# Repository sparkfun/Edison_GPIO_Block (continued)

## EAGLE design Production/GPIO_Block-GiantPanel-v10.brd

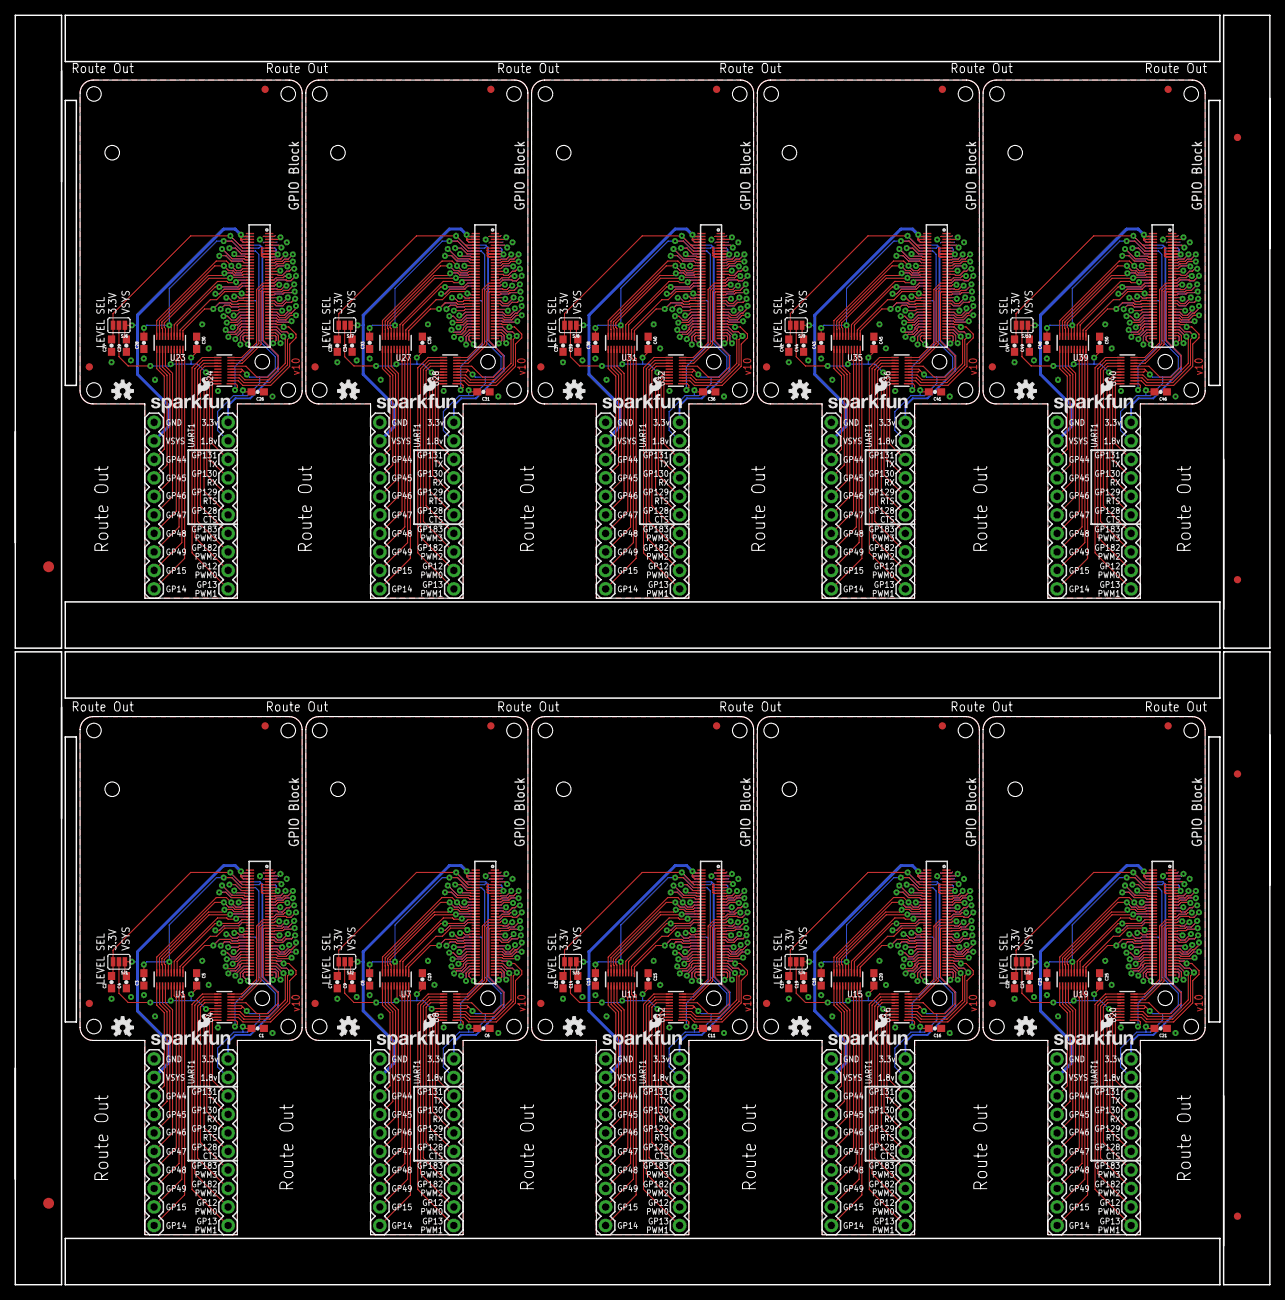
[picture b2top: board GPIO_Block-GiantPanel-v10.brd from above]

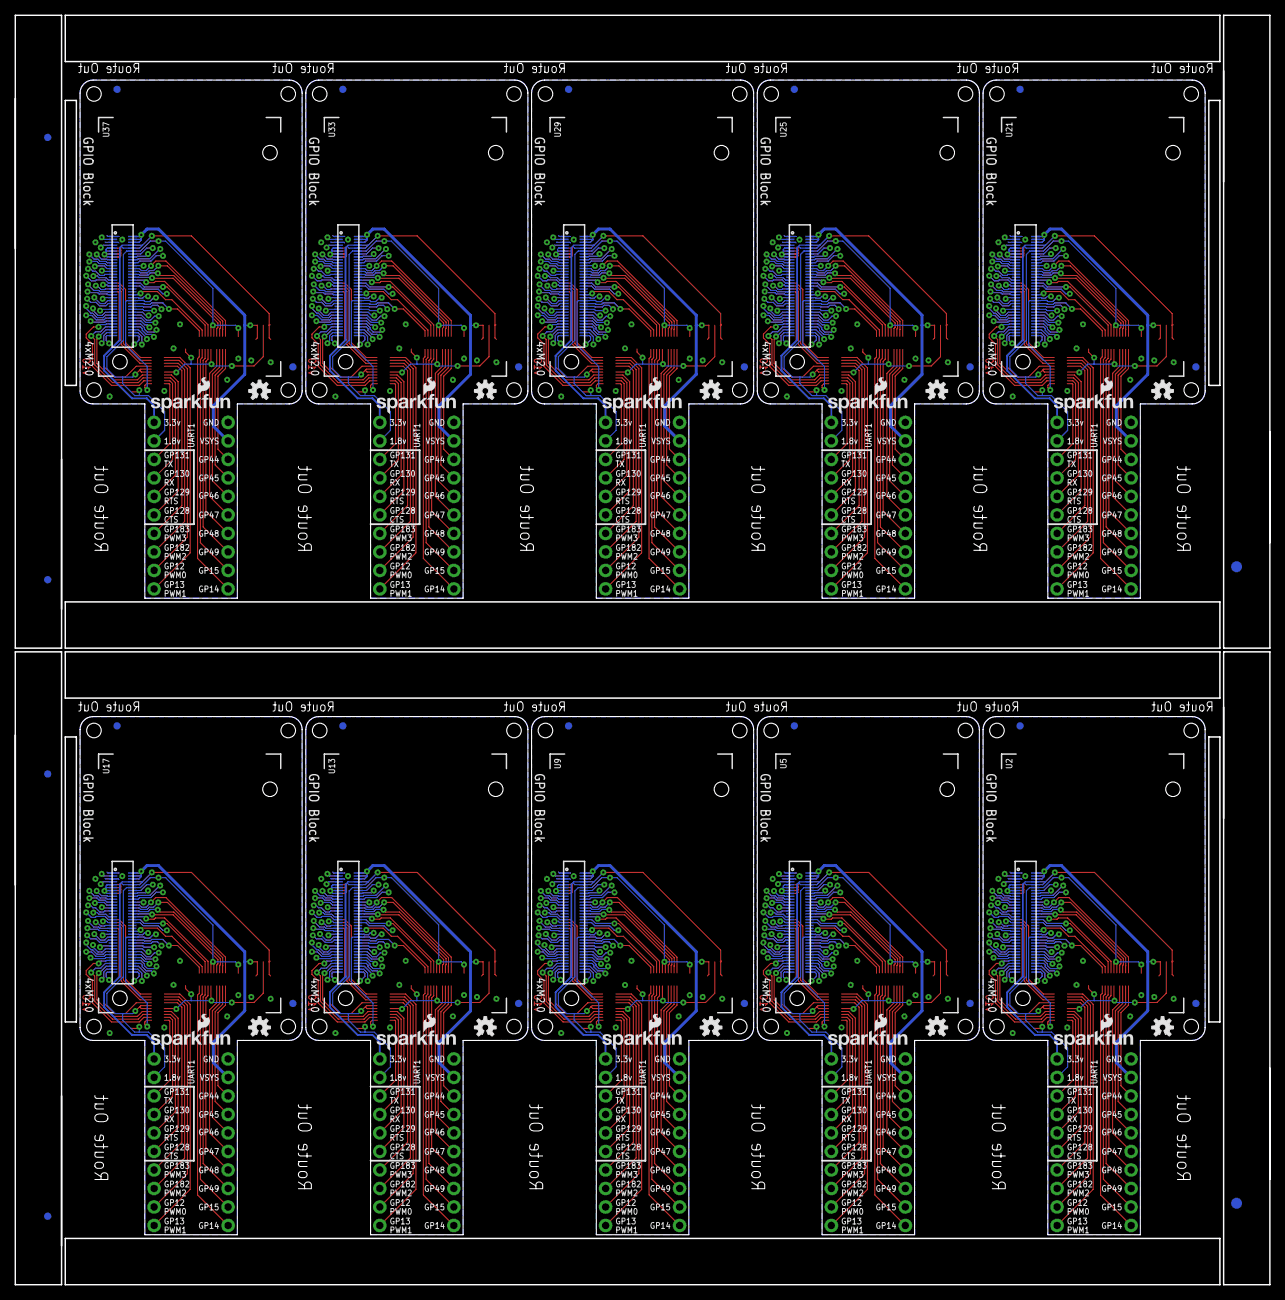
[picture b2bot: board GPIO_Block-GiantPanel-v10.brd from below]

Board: 2 copper layers, 172.2 x 174.2 mm, 212 parts (66 on the bottom side), 750 nets.

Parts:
C1, C2, C3, C4, C5, C6, C7, C8, C9, C10, C11, C12, C13, C14, C15, C16, C17, C18, C19, C20, C21, C22, C23, C24, C25, C26, C27, C28, C29, C30, C31, C32, C33, C34, C35, C36, C37, C38, C39, C40, C41, C42, C43, C44, C45, C46, C47, C48, C49, C50: 0.1uF; 0603-CAP
E$1, E$2, E$9, E$10: FIDUCIAL-1.5X3
E$3, E$4, E$5, E$6, E$7, E$8, E$11, E$12: FIDUCIAL-1X2
FID1, FID2, FID3, FID4, FID5, FID6, FID7, FID8, FID9, FID10, FID11, FID12, FID13, FID14, FID15, FID16, FID17, FID18, FID19, FID20, FID21, FID22, FID23, FID24, FID25, FID26, FID27, FID28, FID29, FID30, FID31, FID32, FID33, FID34, FID35, FID36, FID37, FID38, FID39, FID40: FIDUCIAL1X2; FIDUCIAL-1X2
JP1, JP2, JP3, JP4, JP5, JP6, JP7, JP8, JP9, JP10, JP11, JP12, JP13, JP14, JP15, JP16, JP17, JP18, JP19, JP20: M10"; 1X10
LOGO1, LOGO2, LOGO5, LOGO7, LOGO9, LOGO11, LOGO13, LOGO15, LOGO17, LOGO19, LOGO21, LOGO23, LOGO25, LOGO27, LOGO29, LOGO31, LOGO33, LOGO35, LOGO37, LOGO39: OSHW-LOGOS; OSHW-LOGO-S
LOGO3, LOGO4, LOGO6, LOGO8, LOGO10, LOGO12, LOGO14, LOGO16, LOGO18, LOGO20, LOGO22, LOGO24, LOGO26, LOGO28, LOGO30, LOGO32, LOGO34, LOGO36, LOGO38, LOGO40: SFE_LOGO_NAME_FLAME.1_INCH; SFE_LOGO_NAME_FLAME_.1
SJ1, SJ2, SJ3, SJ4, SJ5, SJ6, SJ7, SJ8, SJ9, SJ10: GPIO Reference Select; PAD-JUMPER-3-2OF3_NC_BY_PASTE_YES_SILK_FULL_BOX
U1, U4, U7, U8, U11, U12, U15, U16, U19, U20, U23, U24, U27, U28, U31, U32, U35, U36, U39, U40: TXB0108; UFDFN-20
U2, U5, U9, U13, U17, U21, U25, U29, U33, U37: EDISON_CONNECTOR_FULLMOUNTING_HOLES; EDISON_DAUGHTER
U3, U6, U10, U14, U18, U22, U26, U30, U34, U38: EDISON_CONNECTOR_FULLHEADER; DF40C-70DP-0.4(51)

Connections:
1.8V: C1.2, C3.2, JP1.9, U1.5, U1.6, U2.12, U3.12, U4.5, U4.6
1.8V1: C6.2, C8.2, JP3.9, U5.12, U6.12, U7.5, U7.6, U8.5, U8.6
1.8V2: C11.2, C13.2, JP5.9, U9.12, U10.12, U11.5, U11.6, U12.5, U12.6
1.8V3: C16.2, C18.2, JP7.9, U13.12, U14.12, U15.5, U15.6, U16.5, U16.6
1.8V4: C21.2, C23.2, JP9.9, U17.12, U18.12, U19.5, U19.6, U20.5, U20.6
1.8V5: C26.2, C28.2, JP11.9, U21.12, U22.12, U23.5, U23.6, U24.5, U24.6
1.8V6: C31.2, C33.2, JP13.9, U25.12, U26.12, U27.5, U27.6, U28.5, U28.6
1.8V7: C36.2, C38.2, JP15.9, U29.12, U30.12, U31.5, U31.6, U32.5, U32.6
1.8V8: C41.2, C43.2, JP17.9, U33.12, U34.12, U35.5, U35.6, U36.5, U36.6
1.8V9: C46.2, C48.2, JP19.9, U37.12, U38.12, U39.5, U39.6, U40.5, U40.6
3.3V: C2.2, JP1.10, SJ1.3, U2.8, U2.10, U3.8, U3.10
3.3V1: C7.2, JP3.10, SJ2.3, U5.8, U5.10, U6.8, U6.10
3.3V2: C12.2, JP5.10, SJ3.3, U9.8, U9.10, U10.8, U10.10
3.3V3: C17.2, JP7.10, SJ4.3, U13.8, U13.10, U14.8, U14.10
3.3V4: C22.2, JP9.10, SJ5.3, U17.8, U17.10, U18.8, U18.10
3.3V5: C27.2, JP11.10, SJ6.3, U21.8, U21.10, U22.8, U22.10
3.3V6: C32.2, JP13.10, SJ7.3, U25.8, U25.10, U26.8, U26.10
3.3V7: C37.2, JP15.10, SJ8.3, U29.8, U29.10, U30.8, U30.10
3.3V8: C42.2, JP17.10, SJ9.3, U33.8, U33.10, U34.8, U34.10
3.3V9: C47.2, JP19.10, SJ10.3, U37.8, U37.10, U38.8, U38.10
DCIN: U2.14, U3.14
DCIN1: U5.14, U6.14
DCIN2: U9.14, U10.14
DCIN3: U13.14, U14.14
DCIN4: U17.14, U18.14
DCIN5: U21.14, U22.14
DCIN6: U25.14, U26.14
DCIN7: U29.14, U30.14
DCIN8: U33.14, U34.14
DCIN9: U37.14, U38.14
FAULT: U2.19, U3.19
FAULT1: U5.19, U6.19
FAULT2: U9.19, U10.19
FAULT3: U13.19, U14.19
FAULT4: U17.19, U18.19
FAULT5: U21.19, U22.19
FAULT6: U25.19, U26.19
FAULT7: U29.19, U30.19
FAULT8: U33.19, U34.19
FAULT9: U37.19, U38.19
FW_RCVR: U2.69, U3.69
FW_RCVR1: U5.69, U6.69
FW_RCVR2: U9.69, U10.69
FW_RCVR3: U13.69, U14.69
FW_RCVR4: U17.69, U18.69
FW_RCVR5: U21.69, U22.69
FW_RCVR6: U25.69, U26.69
FW_RCVR7: U29.69, U30.69
FW_RCVR8: U33.69, U34.69
FW_RCVR9: U37.69, U38.69
GND: C1.1, C2.1, C3.1, C4.1, C5.1, JP2.10, U1.15, U2.1, U2.5, U2.9, U2.11, U2.13, U2.15, U3.1, U3.5, U3.9, U3.11, U3.13, U3.15, U4.15
GND1: C6.1, C7.1, C8.1, C9.1, C10.1, JP4.10, U5.1, U5.5, U5.9, U5.11, U5.13, U5.15, U6.1, U6.5, U6.9, U6.11, U6.13, U6.15, U7.15, U8.15
GND2: C11.1, C12.1, C13.1, C14.1, C15.1, JP6.10, U9.1, U9.5, U9.9, U9.11, U9.13, U9.15, U10.1, U10.5, U10.9, U10.11, U10.13, U10.15, U11.15, U12.15
GND3: C16.1, C17.1, C18.1, C19.1, C20.1, JP8.10, U13.1, U13.5, U13.9, U13.11, U13.13, U13.15, U14.1, U14.5, U14.9, U14.11, U14.13, U14.15, U15.15, U16.15
GND4: C21.1, C22.1, C23.1, C24.1, C25.1, JP10.10, U17.1, U17.5, U17.9, U17.11, U17.13, U17.15, U18.1, U18.5, U18.9, U18.11, U18.13, U18.15, U19.15, U20.15
GND5: C26.1, C27.1, C28.1, C29.1, C30.1, JP12.10, U21.1, U21.5, U21.9, U21.11, U21.13, U21.15, U22.1, U22.5, U22.9, U22.11, U22.13, U22.15, U23.15, U24.15
GND6: C31.1, C32.1, C33.1, C34.1, C35.1, JP14.10, U25.1, U25.5, U25.9, U25.11, U25.13, U25.15, U26.1, U26.5, U26.9, U26.11, U26.13, U26.15, U27.15, U28.15
GND7: C36.1, C37.1, C38.1, C39.1, C40.1, JP16.10, U29.1, U29.5, U29.9, U29.11, U29.13, U29.15, U30.1, U30.5, U30.9, U30.11, U30.13, U30.15, U31.15, U32.15
GND8: C41.1, C42.1, C43.1, C44.1, C45.1, JP18.10, U33.1, U33.5, U33.9, U33.11, U33.13, U33.15, U34.1, U34.5, U34.9, U34.11, U34.13, U34.15, U35.15, U36.15
GND9: C46.1, C47.1, C48.1, C49.1, C50.1, JP20.10, U37.1, U37.5, U37.9, U37.11, U37.13, U37.15, U38.1, U38.5, U38.9, U38.11, U38.13, U38.15, U39.15, U40.15
GP1: U5.48, U6.48, U7.1
GP2: U5.42, U6.42, U7.2
GP3: U5.34, U6.34, U7.3
GP4: U5.32, U6.32, U7.4
GP5: U5.30, U6.30, U7.7
GP6: U5.28, U6.28, U7.8
GP7: U5.26, U6.26, U7.9
GP8: U5.25, U6.25
GP9: U5.24, U6.24, U7.10
GP10: U9.48, U10.48, U11.1
GP11: U9.42, U10.42, U11.2
GP12: U9.34, U10.34, U11.3
GP12_PWM0: U2.35, U3.35, U4.9
GP12_PWM1: U5.35, U6.35, U8.9
GP12_PWM2: U9.35, U10.35, U12.9
GP12_PWM3: U13.35, U14.35, U16.9
GP12_PWM4: U17.35, U18.35, U20.9
GP12_PWM5: U21.35, U22.35, U24.9
GP12_PWM6: U25.35, U26.35, U28.9
GP12_PWM7: U29.35, U30.35, U32.9
GP12_PWM8: U33.35, U34.35, U36.9
GP12_PWM9: U37.35, U38.35, U40.9
GP13: U9.32, U10.32, U11.4
GP13_PWM1: U2.33, U3.33, U4.10
GP13_PWM2: U5.33, U6.33, U8.10
GP13_PWM3: U9.33, U10.33, U12.10
GP13_PWM4: U13.33, U14.33, U16.10
GP13_PWM5: U17.33, U18.33, U20.10
GP13_PWM6: U21.33, U22.33, U24.10
GP13_PWM7: U25.33, U26.33, U28.10
GP13_PWM8: U29.33, U30.33, U32.10
GP13_PWM9: U33.33, U34.33, U36.10
GP13_PWM10: U37.33, U38.33, U40.10
GP14: U1.1, U2.48, U3.48
GP15: U1.2, U2.42, U3.42
GP16: U9.30, U10.30, U11.7
GP17: U9.28, U10.28, U11.8
GP18: U9.26, U10.26, U11.9
GP19: U9.25, U10.25
GP19_I2C_1_SCL: U2.41, U3.41
GP19_I2C_1_SCL1: U5.41, U6.41
GP19_I2C_1_SCL2: U9.41, U10.41
GP19_I2C_1_SCL3: U13.41, U14.41
GP19_I2C_1_SCL4: U17.41, U18.41
GP19_I2C_1_SCL5: U21.41, U22.41
GP19_I2C_1_SCL6: U25.41, U26.41
GP19_I2C_1_SCL7: U29.41, U30.41
GP19_I2C_1_SCL8: U33.41, U34.41
GP19_I2C_1_SCL9: U37.41, U38.41
GP20: U9.24, U10.24, U11.10
GP20_I2C_1_SDA: U2.43, U3.43
GP20_I2C_1_SDA1: U5.43, U6.43
GP20_I2C_1_SDA2: U9.43, U10.43
GP20_I2C_1_SDA3: U13.43, U14.43
GP20_I2C_1_SDA4: U17.43, U18.43
GP20_I2C_1_SDA5: U21.43, U22.43
GP20_I2C_1_SDA6: U25.43, U26.43
GP20_I2C_1_SDA7: U29.43, U30.43
GP20_I2C_1_SDA8: U33.43, U34.43
GP20_I2C_1_SDA9: U37.43, U38.43
GP21: U13.48, U14.48, U15.1
GP22: U13.42, U14.42, U15.2
GP23: U13.34, U14.34, U15.3
GP24: U13.32, U14.32, U15.4
GP25: U13.30, U14.30, U15.7
GP26: U13.28, U14.28, U15.8
GP27: U13.26, U14.26, U15.9
GP27_I2C_6_SCL: U2.45, U3.45
GP27_I2C_6_SCL1: U5.45, U6.45
GP27_I2C_6_SCL2: U9.45, U10.45
GP27_I2C_6_SCL3: U13.45, U14.45
GP27_I2C_6_SCL4: U17.45, U18.45
GP27_I2C_6_SCL5: U21.45, U22.45
GP27_I2C_6_SCL6: U25.45, U26.45
GP27_I2C_6_SCL7: U29.45, U30.45
GP27_I2C_6_SCL8: U33.45, U34.45
GP27_I2C_6_SCL9: U37.45, U38.45
GP28: U13.25, U14.25
GP28_I2C_6_SDA: U2.47, U3.47
GP28_I2C_6_SDA1: U5.47, U6.47
GP28_I2C_6_SDA2: U9.47, U10.47
GP28_I2C_6_SDA3: U13.47, U14.47
GP28_I2C_6_SDA4: U17.47, U18.47
GP28_I2C_6_SDA5: U21.47, U22.47
GP28_I2C_6_SDA6: U25.47, U26.47
GP28_I2C_6_SDA7: U29.47, U30.47
GP28_I2C_6_SDA8: U33.47, U34.47
GP28_I2C_6_SDA9: U37.47, U38.47
GP29: U13.24, U14.24, U15.10
GP30: U17.48, U18.48, U19.1
GP31: U17.42, U18.42, U19.2
GP32: U17.34, U18.34, U19.3
GP33: U17.32, U18.32, U19.4
GP34: U17.30, U18.30, U19.7
GP35: U17.28, U18.28, U19.8
GP36: U17.26, U18.26, U19.9
GP37: U17.25, U18.25
GP38: U17.24, U18.24, U19.10
GP39: U21.48, U22.48, U23.1
GP40: U21.42, U22.42, U23.2
GP40_I2S_2_CLK: U2.52, U3.52
GP40_I2S_2_CLK1: U5.52, U6.52
GP40_I2S_2_CLK2: U9.52, U10.52
GP40_I2S_2_CLK3: U13.52, U14.52
GP40_I2S_2_CLK4: U17.52, U18.52
GP40_I2S_2_CLK5: U21.52, U22.52
GP40_I2S_2_CLK6: U25.52, U26.52
GP40_I2S_2_CLK7: U29.52, U30.52
GP40_I2S_2_CLK8: U33.52, U34.52
GP40_I2S_2_CLK9: U37.52, U38.52
GP41: U21.34, U22.34, U23.3
GP41_I2S_2_FS: U2.54, U3.54
GP41_I2S_2_FS1: U5.54, U6.54
GP41_I2S_2_FS2: U9.54, U10.54
GP41_I2S_2_FS3: U13.54, U14.54
GP41_I2S_2_FS4: U17.54, U18.54
GP41_I2S_2_FS5: U21.54, U22.54
GP41_I2S_2_FS6: U25.54, U26.54
GP41_I2S_2_FS7: U29.54, U30.54
GP41_I2S_2_FS8: U33.54, U34.54
GP41_I2S_2_FS9: U37.54, U38.54
GP42: U21.32, U22.32, U23.4
GP42_I2S_2_RXD: U2.50, U3.50
GP42_I2S_2_RXD1: U5.50, U6.50
GP42_I2S_2_RXD2: U9.50, U10.50
GP42_I2S_2_RXD3: U13.50, U14.50
GP42_I2S_2_RXD4: U17.50, U18.50
GP42_I2S_2_RXD5: U21.50, U22.50
GP42_I2S_2_RXD6: U25.50, U26.50
GP42_I2S_2_RXD7: U29.50, U30.50
GP42_I2S_2_RXD8: U33.50, U34.50
GP42_I2S_2_RXD9: U37.50, U38.50
GP43: U21.30, U22.30, U23.7
GP43_I2S_2_TXD: U2.56, U3.56
GP43_I2S_2_TXD1: U5.56, U6.56
GP43_I2S_2_TXD2: U9.56, U10.56
GP43_I2S_2_TXD3: U13.56, U14.56
GP43_I2S_2_TXD4: U17.56, U18.56
GP43_I2S_2_TXD5: U21.56, U22.56
GP43_I2S_2_TXD6: U25.56, U26.56
GP43_I2S_2_TXD7: U29.56, U30.56
GP43_I2S_2_TXD8: U33.56, U34.56
GP43_I2S_2_TXD9: U37.56, U38.56
GP44: U1.10, U2.24, U3.24
GP45: U1.9, U2.26, U3.26
GP46: U1.8, U2.28, U3.28
GP47: U1.7, U2.30, U3.30
GP48: U1.4, U2.32, U3.32
GP49: U1.3, U2.34, U3.34
GP50: U21.28, U22.28, U23.8
GP51: U21.26, U22.26, U23.9
GP52: U21.25, U22.25
GP53: U21.24, U22.24, U23.10
GP54: U25.48, U26.48, U27.1
GP55: U25.42, U26.42, U27.2
GP56: U25.34, U26.34, U27.3
GP57: U25.32, U26.32, U27.4
GP58: U25.30, U26.30, U27.7
GP59: U25.28, U26.28, U27.8
GP60: U25.26, U26.26, U27.9
GP61: U25.25, U26.25
GP62: U25.24, U26.24, U27.10
GP63: U29.48, U30.48, U31.1
GP64: U29.42, U30.42, U31.2
GP65: U29.34, U30.34, U31.3
GP66: U29.32, U30.32, U31.4
GP67: U29.30, U30.30, U31.7
GP68: U29.28, U30.28, U31.8
GP69: U29.26, U30.26, U31.9
GP70: U29.25, U30.25
GP71: U29.24, U30.24, U31.10
GP72: U33.48, U34.48, U35.1
GP73: U33.42, U34.42, U35.2
GP74: U33.34, U34.34, U35.3
GP75: U33.32, U34.32, U35.4
GP76: U33.30, U34.30, U35.7
GP77: U33.28, U34.28, U35.8
GP77_SD_0_CD#: U2.60, U3.60
GP77_SD_0_CD#1: U5.60, U6.60
GP77_SD_0_CD#2: U9.60, U10.60
GP77_SD_0_CD#3: U13.60, U14.60
GP77_SD_0_CD#4: U17.60, U18.60
GP77_SD_0_CD#5: U21.60, U22.60
GP77_SD_0_CD#6: U25.60, U26.60
GP77_SD_0_CD#7: U29.60, U30.60
GP77_SD_0_CD#8: U33.60, U34.60
GP77_SD_0_CD#9: U37.60, U38.60
GP78: U33.26, U34.26, U35.9
GP78_SD_0_CLK: U2.58, U3.58
GP78_SD_0_CLK1: U5.58, U6.58
GP78_SD_0_CLK2: U9.58, U10.58
GP78_SD_0_CLK3: U13.58, U14.58
GP78_SD_0_CLK4: U17.58, U18.58
GP78_SD_0_CLK5: U21.58, U22.58
GP78_SD_0_CLK6: U25.58, U26.58
GP78_SD_0_CLK7: U29.58, U30.58
GP78_SD_0_CLK8: U33.58, U34.58
GP78_SD_0_CLK9: U37.58, U38.58
GP79: U33.25, U34.25
GP79_SD_0_CMD: U2.62, U3.62
GP79_SD_0_CMD1: U5.62, U6.62
GP79_SD_0_CMD2: U9.62, U10.62
GP79_SD_0_CMD3: U13.62, U14.62
GP79_SD_0_CMD4: U17.62, U18.62
GP79_SD_0_CMD5: U21.62, U22.62
GP79_SD_0_CMD6: U25.62, U26.62
GP79_SD_0_CMD7: U29.62, U30.62
GP79_SD_0_CMD8: U33.62, U34.62
GP79_SD_0_CMD9: U37.62, U38.62
GP80: U33.24, U34.24, U35.10
GP80_SD_0_DAT0: U2.66, U3.66
GP80_SD_0_DAT1: U5.66, U6.66
GP80_SD_0_DAT2: U9.66, U10.66
GP80_SD_0_DAT3: U13.66, U14.66
GP80_SD_0_DAT4: U17.66, U18.66
GP80_SD_0_DAT5: U21.66, U22.66
GP80_SD_0_DAT6: U25.66, U26.66
GP80_SD_0_DAT7: U29.66, U30.66
GP80_SD_0_DAT8: U33.66, U34.66
GP80_SD_0_DAT9: U37.66, U38.66
GP81: U37.48, U38.48, U39.1
GP81_SD_0_DAT1: U2.70, U3.70
GP81_SD_0_DAT2: U5.70, U6.70
GP81_SD_0_DAT3: U9.70, U10.70
GP81_SD_0_DAT4: U13.70, U14.70
GP81_SD_0_DAT5: U17.70, U18.70
GP81_SD_0_DAT6: U21.70, U22.70
GP81_SD_0_DAT7: U25.70, U26.70
GP81_SD_0_DAT8: U29.70, U30.70
GP81_SD_0_DAT9: U33.70, U34.70
GP81_SD_0_DAT10: U37.70, U38.70
GP82: U37.42, U38.42, U39.2
GP82_SD_0_DAT1: U5.64, U6.64
GP82_SD_0_DAT2: U2.64, U3.64
GP82_SD_0_DAT3: U9.64, U10.64
GP82_SD_0_DAT4: U13.64, U14.64
GP82_SD_0_DAT5: U17.64, U18.64
GP82_SD_0_DAT6: U21.64, U22.64
GP82_SD_0_DAT7: U25.64, U26.64
GP82_SD_0_DAT8: U29.64, U30.64
GP82_SD_0_DAT9: U33.64, U34.64
GP82_SD_0_DAT10: U37.64, U38.64
GP83: U37.34, U38.34, U39.3
GP83_SD_0_DAT1: U5.68, U6.68
GP83_SD_0_DAT2: U9.68, U10.68
GP83_SD_0_DAT3: U2.68, U3.68
GP83_SD_0_DAT4: U13.68, U14.68
GP83_SD_0_DAT5: U17.68, U18.68
GP83_SD_0_DAT6: U21.68, U22.68
GP83_SD_0_DAT7: U25.68, U26.68
GP83_SD_0_DAT8: U29.68, U30.68
GP83_SD_0_DAT9: U33.68, U34.68
GP83_SD_0_DAT10: U37.68, U38.68
GP84: U37.32, U38.32, U39.4
GP84_SD_CLK_FB: U2.44, U3.44
GP84_SD_CLK_FB1: U5.44, U6.44
GP84_SD_CLK_FB2: U9.44, U10.44
GP84_SD_CLK_FB3: U13.44, U14.44
GP84_SD_CLK_FB4: U17.44, U18.44
GP84_SD_CLK_FB5: U21.44, U22.44
GP84_SD_CLK_FB6: U25.44, U26.44
GP84_SD_CLK_FB7: U29.44, U30.44
GP84_SD_CLK_FB8: U33.44, U34.44
GP84_SD_CLK_FB9: U37.44, U38.44
GP85: U37.30, U38.30, U39.7
GP86: U37.28, U38.28, U39.8
GP87: U37.26, U38.26, U39.9
GP88: U37.25, U38.25
GP89: U37.24, U38.24, U39.10
GP109_SPI_2_CLK: U2.55, U3.55
GP109_SPI_2_CLK1: U5.55, U6.55
GP109_SPI_2_CLK2: U9.55, U10.55
GP109_SPI_2_CLK3: U13.55, U14.55
GP109_SPI_2_CLK4: U17.55, U18.55
GP109_SPI_2_CLK5: U21.55, U22.55
GP109_SPI_2_CLK6: U25.55, U26.55
GP109_SPI_2_CLK7: U29.55, U30.55
GP109_SPI_2_CLK8: U33.55, U34.55
GP109_SPI_2_CLK9: U37.55, U38.55
GP110_SPI_2_FS0: U2.53, U3.53
GP110_SPI_2_FS1: U5.53, U6.53
GP110_SPI_2_FS2: U9.53, U10.53
GP110_SPI_2_FS3: U13.53, U14.53
GP110_SPI_2_FS4: U17.53, U18.53
GP110_SPI_2_FS5: U21.53, U22.53
GP110_SPI_2_FS6: U25.53, U26.53
GP110_SPI_2_FS7: U29.53, U30.53
GP110_SPI_2_FS8: U33.53, U34.53
GP110_SPI_2_FS9: U37.53, U38.53
GP111_SPI_2_FS1: U2.51, U3.51
GP111_SPI_2_FS2: U5.51, U6.51
GP111_SPI_2_FS3: U9.51, U10.51
GP111_SPI_2_FS4: U13.51, U14.51
GP111_SPI_2_FS5: U17.51, U18.51
GP111_SPI_2_FS6: U21.51, U22.51
GP111_SPI_2_FS7: U25.51, U26.51
GP111_SPI_2_FS8: U29.51, U30.51
GP111_SPI_2_FS9: U33.51, U34.51
GP111_SPI_2_FS10: U37.51, U38.51
GP114_SPI_2_RXD: U2.59, U3.59
GP114_SPI_2_RXD1: U5.59, U6.59
GP114_SPI_2_RXD2: U9.59, U10.59
GP114_SPI_2_RXD3: U13.59, U14.59
GP114_SPI_2_RXD4: U17.59, U18.59
GP114_SPI_2_RXD5: U21.59, U22.59
GP114_SPI_2_RXD6: U25.59, U26.59
GP114_SPI_2_RXD7: U29.59, U30.59
GP114_SPI_2_RXD8: U33.59, U34.59
GP114_SPI_2_RXD9: U37.59, U38.59
GP115_SPI_2_TXD: U2.57, U3.57
GP115_SPI_2_TXD1: U5.57, U6.57
GP115_SPI_2_TXD2: U9.57, U10.57
GP115_SPI_2_TXD3: U13.57, U14.57
GP115_SPI_2_TXD4: U17.57, U18.57
GP115_SPI_2_TXD5: U21.57, U22.57
GP115_SPI_2_TXD6: U25.57, U26.57
GP115_SPI_2_TXD7: U29.57, U30.57
GP115_SPI_2_TXD8: U33.57, U34.57
GP115_SPI_2_TXD9: U37.57, U38.57
GP128_UART_1_CTS: U2.65, U3.65, U4.4
GP128_UART_1_CTS1: U5.65, U6.65, U8.4
GP128_UART_1_CTS2: U9.65, U10.65, U12.4
GP128_UART_1_CTS3: U13.65, U14.65, U16.4
GP128_UART_1_CTS4: U17.65, U18.65, U20.4
GP128_UART_1_CTS5: U21.65, U22.65, U24.4
GP128_UART_1_CTS6: U25.65, U26.65, U28.4
GP128_UART_1_CTS7: U29.65, U30.65, U32.4
GP128_UART_1_CTS8: U33.65, U34.65, U36.4
GP128_UART_1_CTS9: U37.65, U38.65, U40.4
GP129_UART_1_RTS: U2.63, U3.63, U4.3
GP129_UART_1_RTS1: U5.63, U6.63, U8.3
GP129_UART_1_RTS2: U9.63, U10.63, U12.3
GP129_UART_1_RTS3: U13.63, U14.63, U16.3
GP129_UART_1_RTS4: U17.63, U18.63, U20.3
GP129_UART_1_RTS5: U21.63, U22.63, U24.3
GP129_UART_1_RTS6: U25.63, U26.63, U28.3
GP129_UART_1_RTS7: U29.63, U30.63, U32.3
GP129_UART_1_RTS8: U33.63, U34.63, U36.3
GP129_UART_1_RTS9: U37.63, U38.63, U40.3
GP130_UART_1_RX: U2.61, U3.61, U4.2
GP130_UART_1_RX1: U5.61, U6.61, U8.2
GP130_UART_1_RX2: U9.61, U10.61, U12.2
GP130_UART_1_RX3: U13.61, U14.61, U16.2
GP130_UART_1_RX4: U17.61, U18.61, U20.2
GP130_UART_1_RX5: U21.61, U22.61, U24.2
GP130_UART_1_RX6: U25.61, U26.61, U28.2
GP130_UART_1_RX7: U29.61, U30.61, U32.2
GP130_UART_1_RX8: U33.61, U34.61, U36.2
GP130_UART_1_RX9: U37.61, U38.61, U40.2
GP131_UART_1_TX: U2.46, U3.46, U4.1
GP131_UART_1_TX1: U5.46, U6.46, U8.1
GP131_UART_1_TX2: U9.46, U10.46, U12.1
GP131_UART_1_TX3: U13.46, U14.46, U16.1
GP131_UART_1_TX4: U17.46, U18.46, U20.1
GP131_UART_1_TX5: U21.46, U22.46, U24.1
GP131_UART_1_TX6: U25.46, U26.46, U28.1
GP131_UART_1_TX7: U29.46, U30.46, U32.1
GP131_UART_1_TX8: U33.46, U34.46, U36.1
GP131_UART_1_TX9: U37.46, U38.46, U40.1
GP134_UART_2_RX: U2.22, U3.22
GP134_UART_2_RX1: U5.22, U6.22
GP134_UART_2_RX2: U9.22, U10.22
GP134_UART_2_RX3: U13.22, U14.22
GP134_UART_2_RX4: U17.22, U18.22
GP134_UART_2_RX5: U21.22, U22.22
GP134_UART_2_RX6: U25.22, U26.22
GP134_UART_2_RX7: U29.22, U30.22
GP134_UART_2_RX8: U33.22, U34.22
GP134_UART_2_RX9: U37.22, U38.22
GP135_UART_2_TX: U2.27, U3.27
GP135_UART_2_TX1: U5.27, U6.27
GP135_UART_2_TX2: U9.27, U10.27
GP135_UART_2_TX3: U13.27, U14.27
GP135_UART_2_TX4: U17.27, U18.27
GP135_UART_2_TX5: U21.27, U22.27
GP135_UART_2_TX6: U25.27, U26.27
GP135_UART_2_TX7: U29.27, U30.27
GP135_UART_2_TX8: U33.27, U34.27
GP135_UART_2_TX9: U37.27, U38.27
GP165: U2.25, U3.25
GP182_PWM1: U5.37, U6.37, U8.8
GP182_PWM2: U2.37, U3.37, U4.8
GP182_PWM3: U9.37, U10.37, U12.8
GP182_PWM4: U13.37, U14.37, U16.8
GP182_PWM5: U17.37, U18.37, U20.8
GP182_PWM6: U21.37, U22.37, U24.8
GP182_PWM7: U25.37, U26.37, U28.8
GP182_PWM8: U29.37, U30.37, U32.8
GP182_PWM9: U33.37, U34.37, U36.8
GP182_PWM10: U37.37, U38.37, U40.8
GP183_PWM1: U5.39, U6.39, U8.7
GP183_PWM2: U9.39, U10.39, U12.7
GP183_PWM3: U2.39, U3.39, U4.7
GP183_PWM4: U13.39, U14.39, U16.7
GP183_PWM5: U17.39, U18.39, U20.7
GP183_PWM6: U21.39, U22.39, U24.7
GP183_PWM7: U25.39, U26.39, U28.7
GP183_PWM8: U29.39, U30.39, U32.7
GP183_PWM9: U33.39, U34.39, U36.7
GP183_PWM10: U37.39, U38.39, U40.7
GPIO_REFERENCE_SELECT: C5.2, SJ1.2, U1.16, U4.16
GPIO_REFERENCE_SELECT1: C10.2, SJ2.2, U7.16, U8.16
GPIO_REFERENCE_SELECT2: C15.2, SJ3.2, U11.16, U12.16
GPIO_REFERENCE_SELECT3: C20.2, SJ4.2, U15.16, U16.16
GPIO_REFERENCE_SELECT4: C25.2, SJ5.2, U19.16, U20.16
GPIO_REFERENCE_SELECT5: C30.2, SJ6.2, U23.16, U24.16
GPIO_REFERENCE_SELECT6: C35.2, SJ7.2, U27.16, U28.16
GPIO_REFERENCE_SELECT7: C40.2, SJ8.2, U31.16, U32.16
GPIO_REFERENCE_SELECT8: C45.2, SJ9.2, U35.16, U36.16
GPIO_REFERENCE_SELECT9: C50.2, SJ10.2, U39.16, U40.16
MSIC_SLP_CLK: U2.7, U3.7
MSIC_SLP_CLK1: U5.7, U6.7
MSIC_SLP_CLK2: U9.7, U10.7
MSIC_SLP_CLK3: U13.7, U14.7
MSIC_SLP_CLK4: U17.7, U18.7
MSIC_SLP_CLK5: U21.7, U22.7
MSIC_SLP_CLK6: U25.7, U26.7
MSIC_SLP_CLK7: U29.7, U30.7
MSIC_SLP_CLK8: U33.7, U34.7
MSIC_SLP_CLK9: U37.7, U38.7
unnamed: JP2.8, U1.11
unnamed: JP2.7, U1.12
unnamed: JP2.6, U1.13
unnamed: JP2.5, U1.14
unnamed: JP2.4, U1.17
unnamed: JP2.3, U1.18
unnamed: JP2.2, U1.19
unnamed: JP2.1, U1.20
unnamed: JP4.8, U7.11
unnamed: JP4.7, U7.12
unnamed: JP1.4, U4.14
unnamed: JP1.3, U4.13
unnamed: JP1.2, U4.12
unnamed: JP1.1, U4.11
unnamed: JP1.5, U4.17
unnamed: JP1.6, U4.18
unnamed: JP1.7, U4.19
unnamed: JP1.8, U4.20
unnamed: JP4.6, U7.13
unnamed: JP4.5, U7.14
unnamed: JP4.4, U7.17
unnamed: JP4.3, U7.18
unnamed: JP4.2, U7.19
unnamed: JP4.1, U7.20
unnamed: JP3.5, U8.17
unnamed: JP3.6, U8.18
unnamed: JP3.7, U8.19
unnamed: JP3.8, U8.20
unnamed: JP3.4, U8.14
unnamed: JP3.3, U8.13
unnamed: JP3.2, U8.12
unnamed: JP3.1, U8.11
unnamed: JP6.8, U11.11
unnamed: JP6.7, U11.12
unnamed: JP6.6, U11.13
unnamed: JP6.5, U11.14
unnamed: JP6.4, U11.17
unnamed: JP6.3, U11.18
unnamed: JP6.2, U11.19
unnamed: JP6.1, U11.20
unnamed: JP5.5, U12.17
unnamed: JP5.6, U12.18
unnamed: JP5.7, U12.19
unnamed: JP5.8, U12.20
unnamed: JP5.4, U12.14
unnamed: JP5.3, U12.13
unnamed: JP5.2, U12.12
unnamed: JP5.1, U12.11
unnamed: JP8.8, U15.11
unnamed: JP8.7, U15.12
unnamed: JP8.6, U15.13
unnamed: JP8.5, U15.14
unnamed: JP8.4, U15.17
unnamed: JP8.3, U15.18
unnamed: JP8.2, U15.19
unnamed: JP8.1, U15.20
unnamed: JP7.5, U16.17
unnamed: JP7.6, U16.18
unnamed: JP7.7, U16.19
unnamed: JP7.8, U16.20
unnamed: JP7.4, U16.14
unnamed: JP7.3, U16.13
unnamed: JP7.2, U16.12
unnamed: JP7.1, U16.11
unnamed: JP10.8, U19.11
unnamed: JP10.7, U19.12
unnamed: JP10.6, U19.13
unnamed: JP10.5, U19.14
unnamed: JP10.4, U19.17
unnamed: JP10.3, U19.18
unnamed: JP10.2, U19.19
unnamed: JP10.1, U19.20
unnamed: JP9.5, U20.17
unnamed: JP9.6, U20.18
unnamed: JP9.7, U20.19
unnamed: JP9.8, U20.20
unnamed: JP9.4, U20.14
unnamed: JP9.3, U20.13
unnamed: JP9.2, U20.12
unnamed: JP9.1, U20.11
unnamed: JP12.8, U23.11
unnamed: JP12.7, U23.12
unnamed: JP12.6, U23.13
unnamed: JP12.5, U23.14
unnamed: JP12.4, U23.17
unnamed: JP12.3, U23.18
unnamed: JP12.2, U23.19
unnamed: JP12.1, U23.20
unnamed: JP11.5, U24.17
unnamed: JP11.6, U24.18
unnamed: JP11.7, U24.19
unnamed: JP11.8, U24.20
unnamed: JP11.4, U24.14
unnamed: JP11.3, U24.13
unnamed: JP11.2, U24.12
unnamed: JP11.1, U24.11
unnamed: JP14.8, U27.11
unnamed: JP14.7, U27.12
unnamed: JP14.6, U27.13
unnamed: JP14.5, U27.14
unnamed: JP14.4, U27.17
unnamed: JP14.3, U27.18
unnamed: JP14.2, U27.19
unnamed: JP14.1, U27.20
unnamed: JP13.5, U28.17
unnamed: JP13.6, U28.18
unnamed: JP13.7, U28.19
unnamed: JP13.8, U28.20
unnamed: JP13.4, U28.14
unnamed: JP13.3, U28.13
unnamed: JP13.2, U28.12
unnamed: JP13.1, U28.11
unnamed: JP16.8, U31.11
unnamed: JP16.7, U31.12
unnamed: JP16.6, U31.13
unnamed: JP16.5, U31.14
unnamed: JP16.4, U31.17
unnamed: JP16.3, U31.18
unnamed: JP16.2, U31.19
unnamed: JP16.1, U31.20
unnamed: JP15.5, U32.17
unnamed: JP15.6, U32.18
unnamed: JP15.7, U32.19
unnamed: JP15.8, U32.20
unnamed: JP15.4, U32.14
unnamed: JP15.3, U32.13
unnamed: JP15.2, U32.12
unnamed: JP15.1, U32.11
unnamed: JP18.8, U35.11
unnamed: JP18.7, U35.12
unnamed: JP18.6, U35.13
unnamed: JP18.5, U35.14
unnamed: JP18.4, U35.17
unnamed: JP18.3, U35.18
unnamed: JP18.2, U35.19
unnamed: JP18.1, U35.20
unnamed: JP17.5, U36.17
unnamed: JP17.6, U36.18
unnamed: JP17.7, U36.19
unnamed: JP17.8, U36.20
unnamed: JP17.4, U36.14
unnamed: JP17.3, U36.13
unnamed: JP17.2, U36.12
unnamed: JP17.1, U36.11
unnamed: JP20.8, U39.11
unnamed: JP20.7, U39.12
unnamed: JP20.6, U39.13
unnamed: JP20.5, U39.14
unnamed: JP20.4, U39.17
unnamed: JP20.3, U39.18
unnamed: JP20.2, U39.19
unnamed: JP20.1, U39.20
unnamed: JP19.5, U40.17
unnamed: JP19.6, U40.18
unnamed: JP19.7, U40.19
unnamed: JP19.8, U40.20
unnamed: JP19.4, U40.14
unnamed: JP19.3, U40.13
unnamed: JP19.2, U40.12
unnamed: JP19.1, U40.11
OSC_CLK_OUT: U2.67, U3.67
OSC_CLK_OUT1: U5.67, U6.67
OSC_CLK_OUT2: U9.67, U10.67
OSC_CLK_OUT3: U13.67, U14.67
OSC_CLK_OUT4: U17.67, U18.67
OSC_CLK_OUT5: U21.67, U22.67
OSC_CLK_OUT6: U25.67, U26.67
OSC_CLK_OUT7: U29.67, U30.67
OSC_CLK_OUT8: U33.67, U34.67
OSC_CLK_OUT9: U37.67, U38.67
PSW: U2.21, U3.21
PSW1: U5.21, U6.21
PSW2: U9.21, U10.21
PSW3: U13.21, U14.21
PSW4: U17.21, U18.21
PSW5: U21.21, U22.21
PSW6: U25.21, U26.21
PSW7: U29.21, U30.21
PSW8: U33.21, U34.21
PSW9: U37.21, U38.21
PWRBTN#: U2.17, U3.17
PWRBTN#1: U5.17, U6.17
PWRBTN#2: U9.17, U10.17
PWRBTN#3: U13.17, U14.17
PWRBTN#4: U17.17, U18.17
PWRBTN#5: U21.17, U22.17
PWRBTN#6: U25.17, U26.17
PWRBTN#7: U29.17, U30.17
PWRBTN#8: U33.17, U34.17
PWRBTN#9: U37.17, U38.17
RCVR_MODE: U2.31, U3.31
RCVR_MODE1: U5.31, U6.31
RCVR_MODE2: U9.31, U10.31
RCVR_MODE3: U13.31, U14.31
RCVR_MODE4: U17.31, U18.31
RCVR_MODE5: U21.31, U22.31
RCVR_MODE6: U25.31, U26.31
RCVR_MODE7: U29.31, U30.31
RCVR_MODE8: U33.31, U34.31
RCVR_MODE9: U37.31, U38.31
RESET_OUT#: U2.36, U3.36
RESET_OUT#1: U5.36, U6.36
RESET_OUT#2: U9.36, U10.36
RESET_OUT#3: U13.36, U14.36
RESET_OUT#4: U17.36, U18.36
RESET_OUT#5: U21.36, U22.36
RESET_OUT#6: U25.36, U26.36
RESET_OUT#7: U29.36, U30.36
RESET_OUT#8: U33.36, U34.36
RESET_OUT#9: U37.36, U38.36
USB_DN: U2.18, U3.18
USB_DN1: U5.18, U6.18
USB_DN2: U9.18, U10.18
USB_DN3: U13.18, U14.18
USB_DN4: U17.18, U18.18
USB_DN5: U21.18, U22.18
USB_DN6: U25.18, U26.18
USB_DN7: U29.18, U30.18
USB_DN8: U33.18, U34.18
USB_DN9: U37.18, U38.18
USB_DP: U2.16, U3.16
USB_DP1: U5.16, U6.16
USB_DP2: U9.16, U10.16
USB_DP3: U13.16, U14.16
USB_DP4: U17.16, U18.16
USB_DP5: U21.16, U22.16
USB_DP6: U25.16, U26.16
USB_DP7: U29.16, U30.16
USB_DP8: U33.16, U34.16
USB_DP9: U37.16, U38.16
USB_ID: U2.3, U3.3
USB_ID1: U5.3, U6.3
USB_ID2: U9.3, U10.3
USB_ID3: U13.3, U14.3
USB_ID4: U17.3, U18.3
USB_ID5: U21.3, U22.3
USB_ID6: U25.3, U26.3
USB_ID7: U29.3, U30.3
USB_ID8: U33.3, U34.3
USB_ID9: U37.3, U38.3
USB_VBUS: U2.20, U3.20
USB_VBUS1: U5.20, U6.20
USB_VBUS2: U9.20, U10.20
USB_VBUS3: U13.20, U14.20
USB_VBUS4: U17.20, U18.20
USB_VBUS5: U21.20, U22.20
USB_VBUS6: U25.20, U26.20
USB_VBUS7: U29.20, U30.20
USB_VBUS8: U33.20, U34.20
USB_VBUS9: U37.20, U38.20
VSYS: C4.2, JP2.9, SJ1.1, U2.2, U2.4, U2.6, U3.2, U3.4, U3.6
VSYS1: C9.2, JP4.9, SJ2.1, U5.2, U5.4, U5.6, U6.2, U6.4, U6.6
VSYS2: C14.2, JP6.9, SJ3.1, U9.2, U9.4, U9.6, U10.2, U10.4, U10.6
VSYS3: C19.2, JP8.9, SJ4.1, U13.2, U13.4, U13.6, U14.2, U14.4, U14.6
VSYS4: C24.2, JP10.9, SJ5.1, U17.2, U17.4, U17.6, U18.2, U18.4, U18.6
VSYS5: C29.2, JP12.9, SJ6.1, U21.2, U21.4, U21.6, U22.2, U22.4, U22.6
VSYS6: C34.2, JP14.9, SJ7.1, U25.2, U25.4, U25.6, U26.2, U26.4, U26.6
VSYS7: C39.2, JP16.9, SJ8.1, U29.2, U29.4, U29.6, U30.2, U30.4, U30.6
VSYS8: C44.2, JP18.9, SJ9.1, U33.2, U33.4, U33.6, U34.2, U34.4, U34.6
VSYS9: C49.2, JP20.9, SJ10.1, U37.2, U37.4, U37.6, U38.2, U38.4, U38.6
V_BAT_BKUP: U2.23, U3.23
V_BAT_BKUP1: U5.23, U6.23
V_BAT_BKUP2: U9.23, U10.23
V_BAT_BKUP3: U13.23, U14.23
V_BAT_BKUP4: U17.23, U18.23
V_BAT_BKUP5: U21.23, U22.23
V_BAT_BKUP6: U25.23, U26.23
V_BAT_BKUP7: U29.23, U30.23
V_BAT_BKUP8: U33.23, U34.23
V_BAT_BKUP9: U37.23, U38.23

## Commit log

2014-08-09 initial commit with template renamed.
2014-08-09 completed layout of GPIO Ready for review
2014-08-09 added rev number to SCH
2014-08-12 removed Edzzanine from name
2014-08-28 Updated Readme with small description
2014-09-23 added level shifters with the ability to select from vsys and 3.3v cleaned up copper pours changed name on board and files added DCIN pin cleaned up units of board.
2014-09-25 file cleanup
2014-10-01 corrected silk error CTS pin on UART was incorrectly numbered
2014-10-16 t/bRestrict between connector pads. (v10)
2014-10-16 Re-routing 3.3v line
2014-10-17 Adding silk to bottom. Slight trace re-routes.
2014-10-17 adding thermal to staking pad
2014-10-17 removed stray Bplace from Package
2014-10-17 Ready for reds No changes No known to-do items
2014-10-20 created v10 panels
2014-10-20 added Route Out for GP
2014-12-03 Updated Readme.
2015-04-01 Updating README and directory file name
